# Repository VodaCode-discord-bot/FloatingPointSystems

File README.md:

# Floating Point Systems

A repository for gathering documentation and understanding Floating-Point-Systems machines.

> [!NOTE]
> This documentation is incomplete and will be expanded as more information becomes available.

> [!WARNING]
> This README needs to be verified by the REPO owner: Nakazoto. 

## Overview

This project contains datasheets, documentation, and code related to floating-point-sytems machines.

## Index - For README

1. [Overview](#overview) - Reason What this REPO is for. 
2. [Contents](#contents---of-each-folder) - What is in the Folders.
3. [Index for FPS](#index---for-the-folders) - Folder links.
4. [Contributing](#contributing) - Things to look out for.
    - [Guide on Contributing](#a-little-guide) - A guide on contributing.

## Contents - Of each folder

- Documentation on floating-point-systems
- Some Datasheets
- Photos of Cards, etc
- Code for the Machines

## Index - For the folders

1. [OLD](!Old/) - Folder with old stuff , _A trade of some sort_
2. [AP 120B](AP%20120B/) - Documetation folder for AP 120B, _the predecessor of the FPS 100._
3. [FPS 100](FPS%20100/) - Documetation folder for FPS 100, _the successor of the AP 120B. With redused cards._
4. [FPS 164](FPS%20164/) - Documetation folder for FPS 164, _the favorite machine of Usagi Electric._
5. [FPS 3000](FPS%203000/) - Documetation folder for FPS 3000, _the machine that only 1 still known to exist. And is almost the same as the XP 32 is._
6. [FPS 5000](FPS%205000/) - Documetation folder for FPS 5000, _As mentioned in fps.pdf, this is a family of the AP 120B, just like any other machine._
7. [Random FPS information](Z.%20Others/) - Documetation folder for FPS information, _Like part prices and boardrevisions._
8. [Random PDFs](Z_Brochures/) - Documetation folder for PDFs, _Like product pages and folders._
9. [Boards in FPS Machines](Cully_Dave.txt) - Documetation file for cards, _The card configuration on different machines._
10. [Magazine of some sort](Digital_Design_V12_N06_198206.pdf) - Some sort of Magazine.
11. [Boards](FPS%20Board%20List.txt) - A board series, _with documentation._
12. [Known Surviving](KnownSurviving.txt) - Documetation file for Surviving machines, _With name, place, condition and maybe price ;D_
13. [Want to make a FPS?](NewFPSLayout.txt) - Documetation file for A Complete Card set for AP 120B, _What some people have._

## Contributing

> [!CAUTION]
> This REPO is not meant for harassment, hating or any kind of destroying other people's work! So if you help this repo grow it is appreciated!

### A little guide:

> [!NOTE]
> _There are lots of guides online that explain this in detail._ [LINK](www.DID-NOT-FIND-ONE.com)

1. Create a Fork.
2. Import / Create the file you wanted to contribute.
3. Create a Pull request and explain what you changed.
	- You may have to add you fork (sometimes it does this automatically!)
4. Wait on a response!

> [!IMPORTANT]
> To to achieve your goal it needs to be relevant to the REPO and it's subject.

<!--
NOTE:
INDEX DOES NOT WORK IN EDITOR,
this is not done!
-->

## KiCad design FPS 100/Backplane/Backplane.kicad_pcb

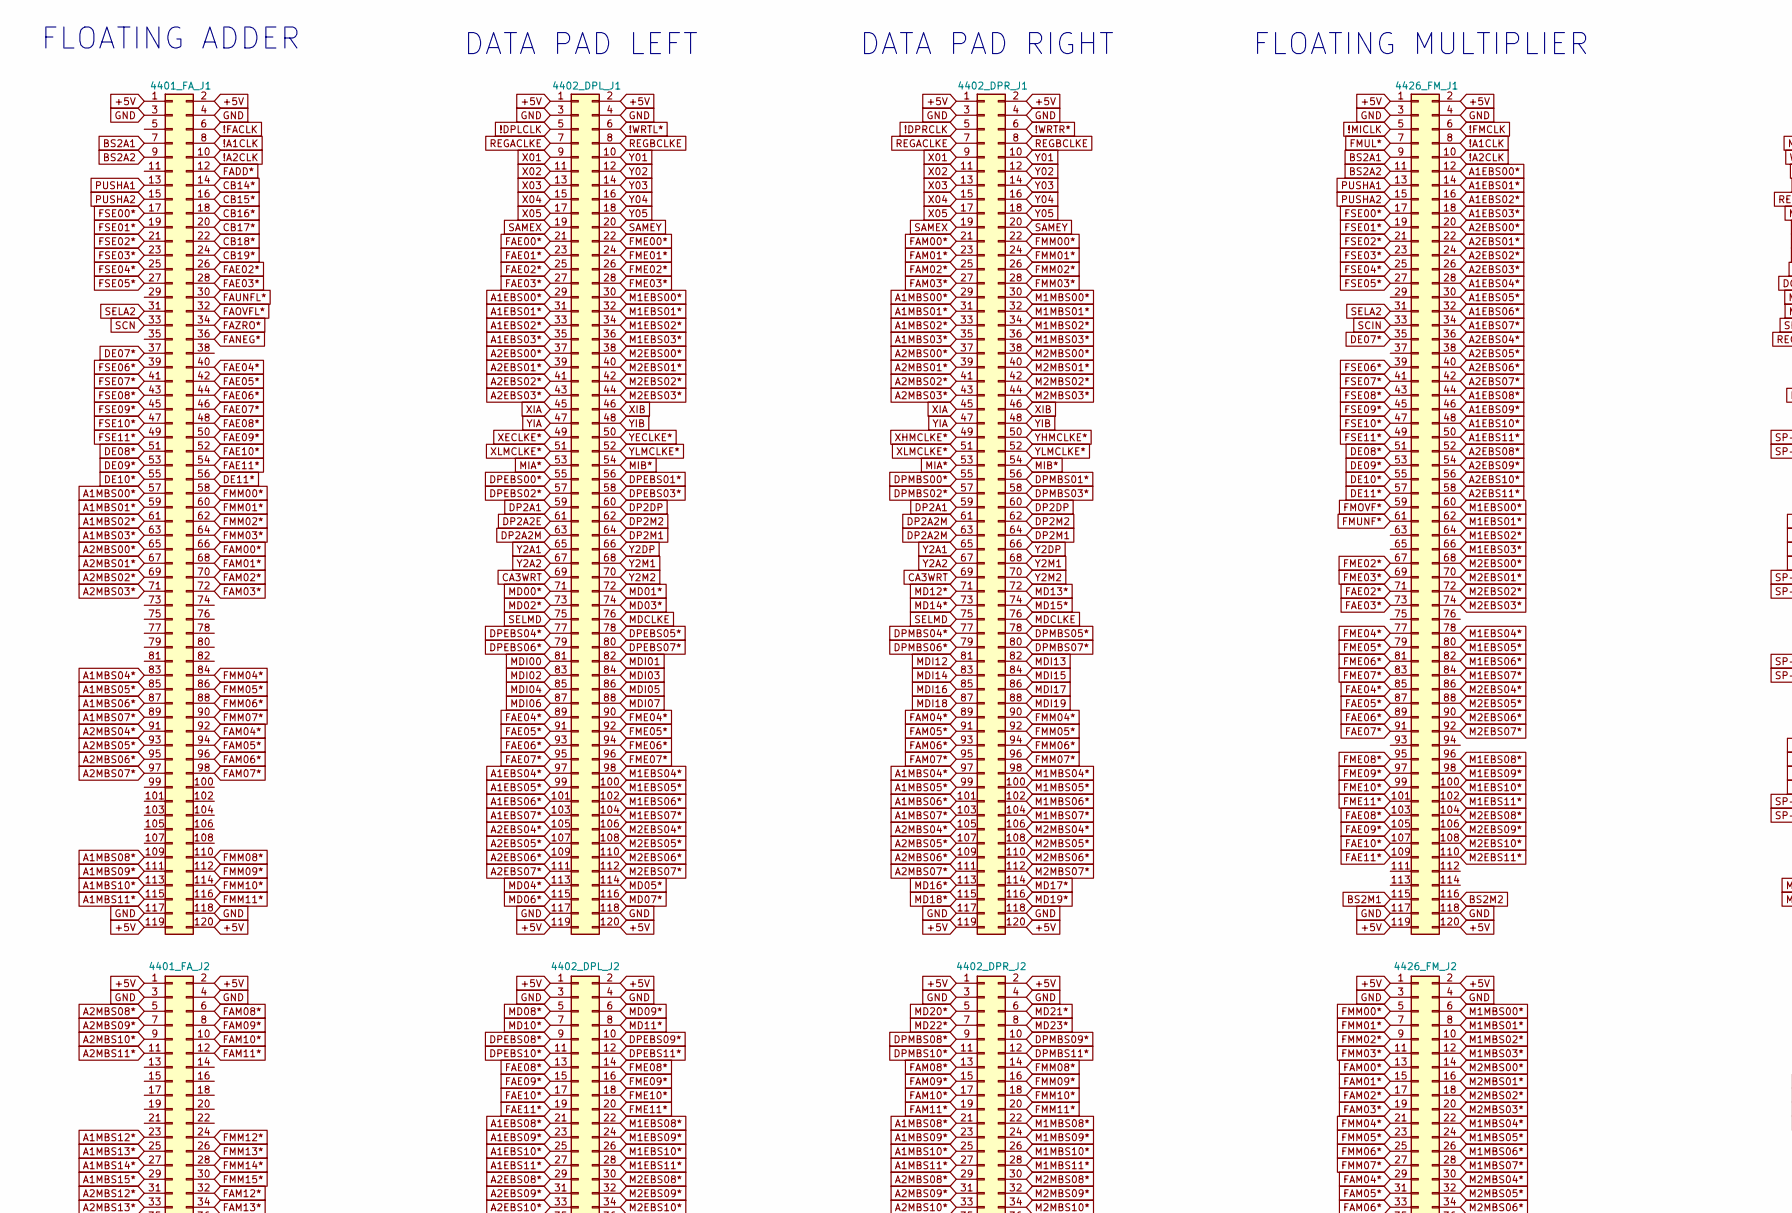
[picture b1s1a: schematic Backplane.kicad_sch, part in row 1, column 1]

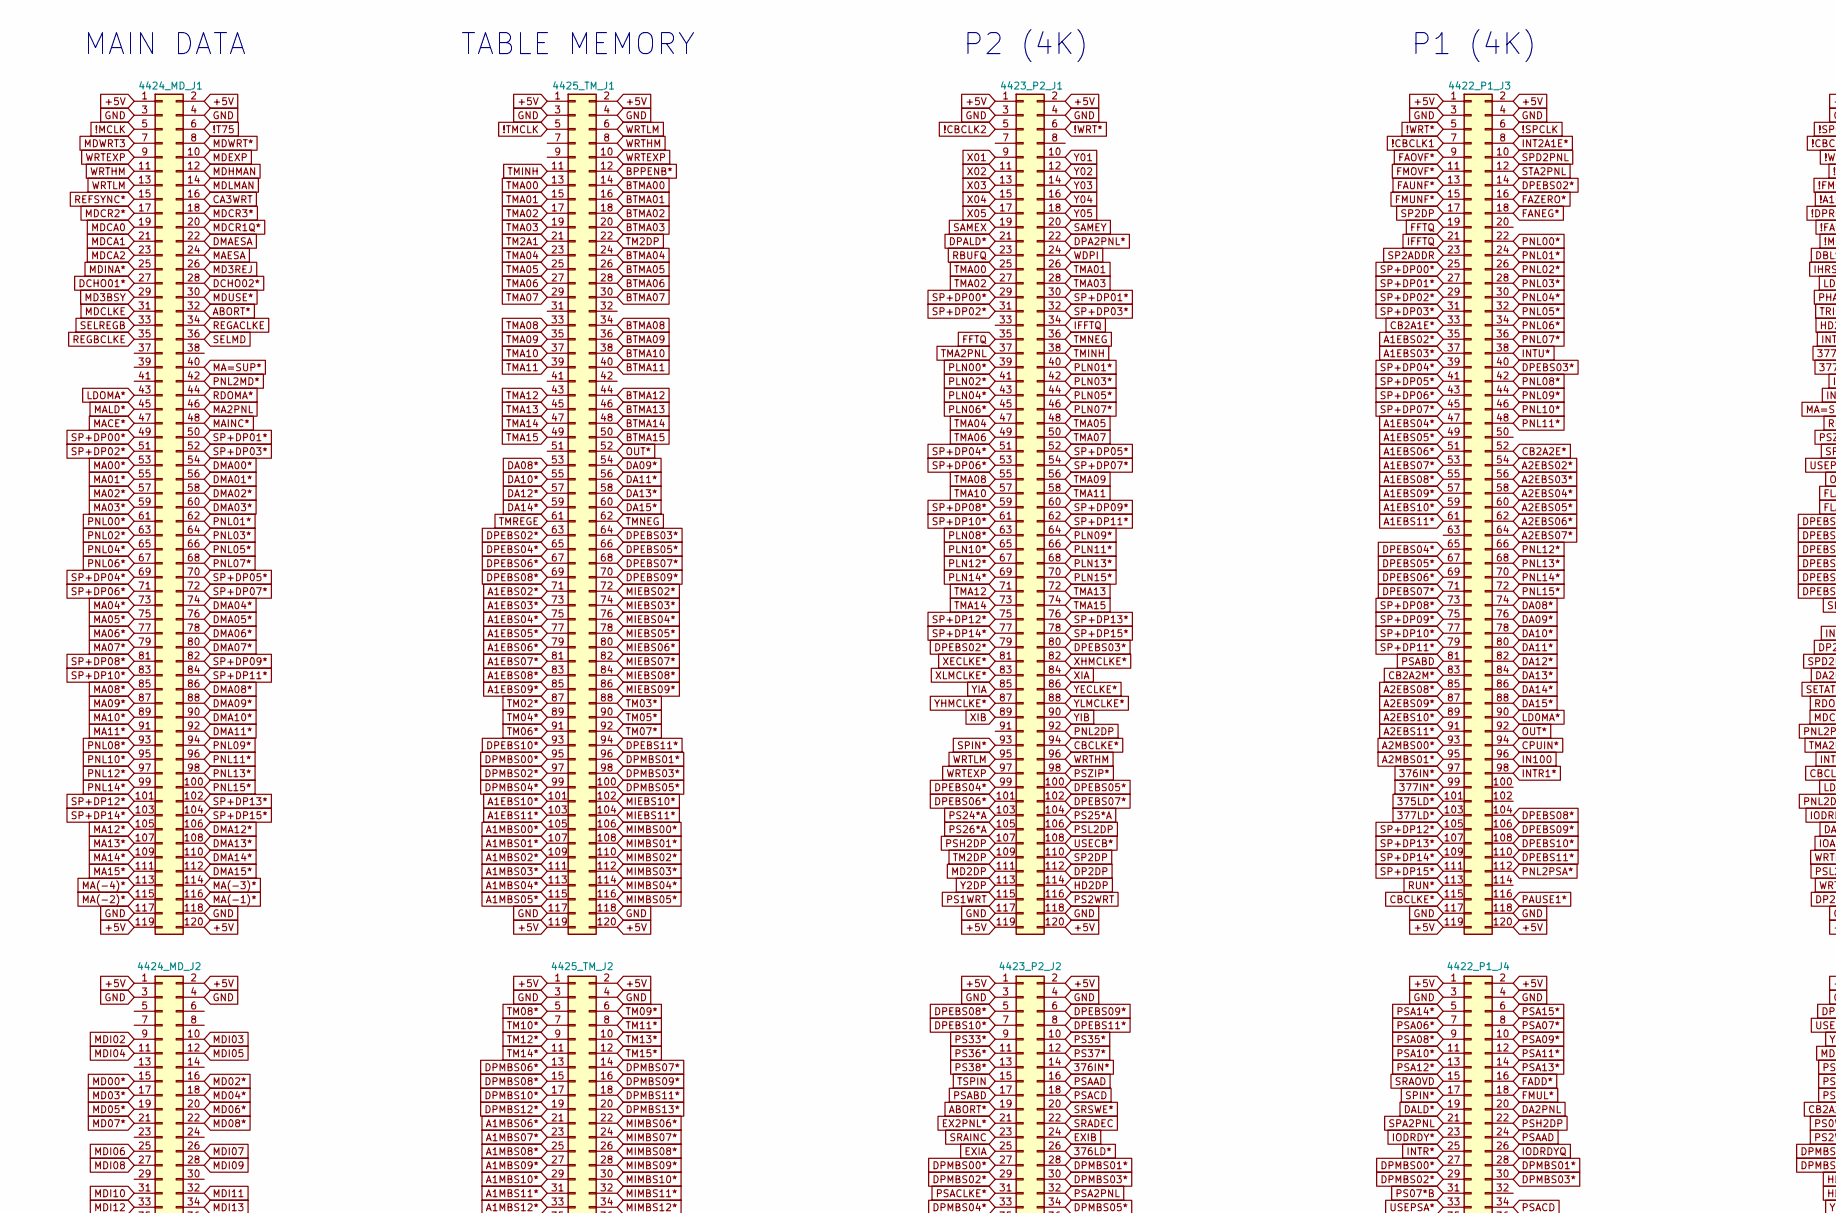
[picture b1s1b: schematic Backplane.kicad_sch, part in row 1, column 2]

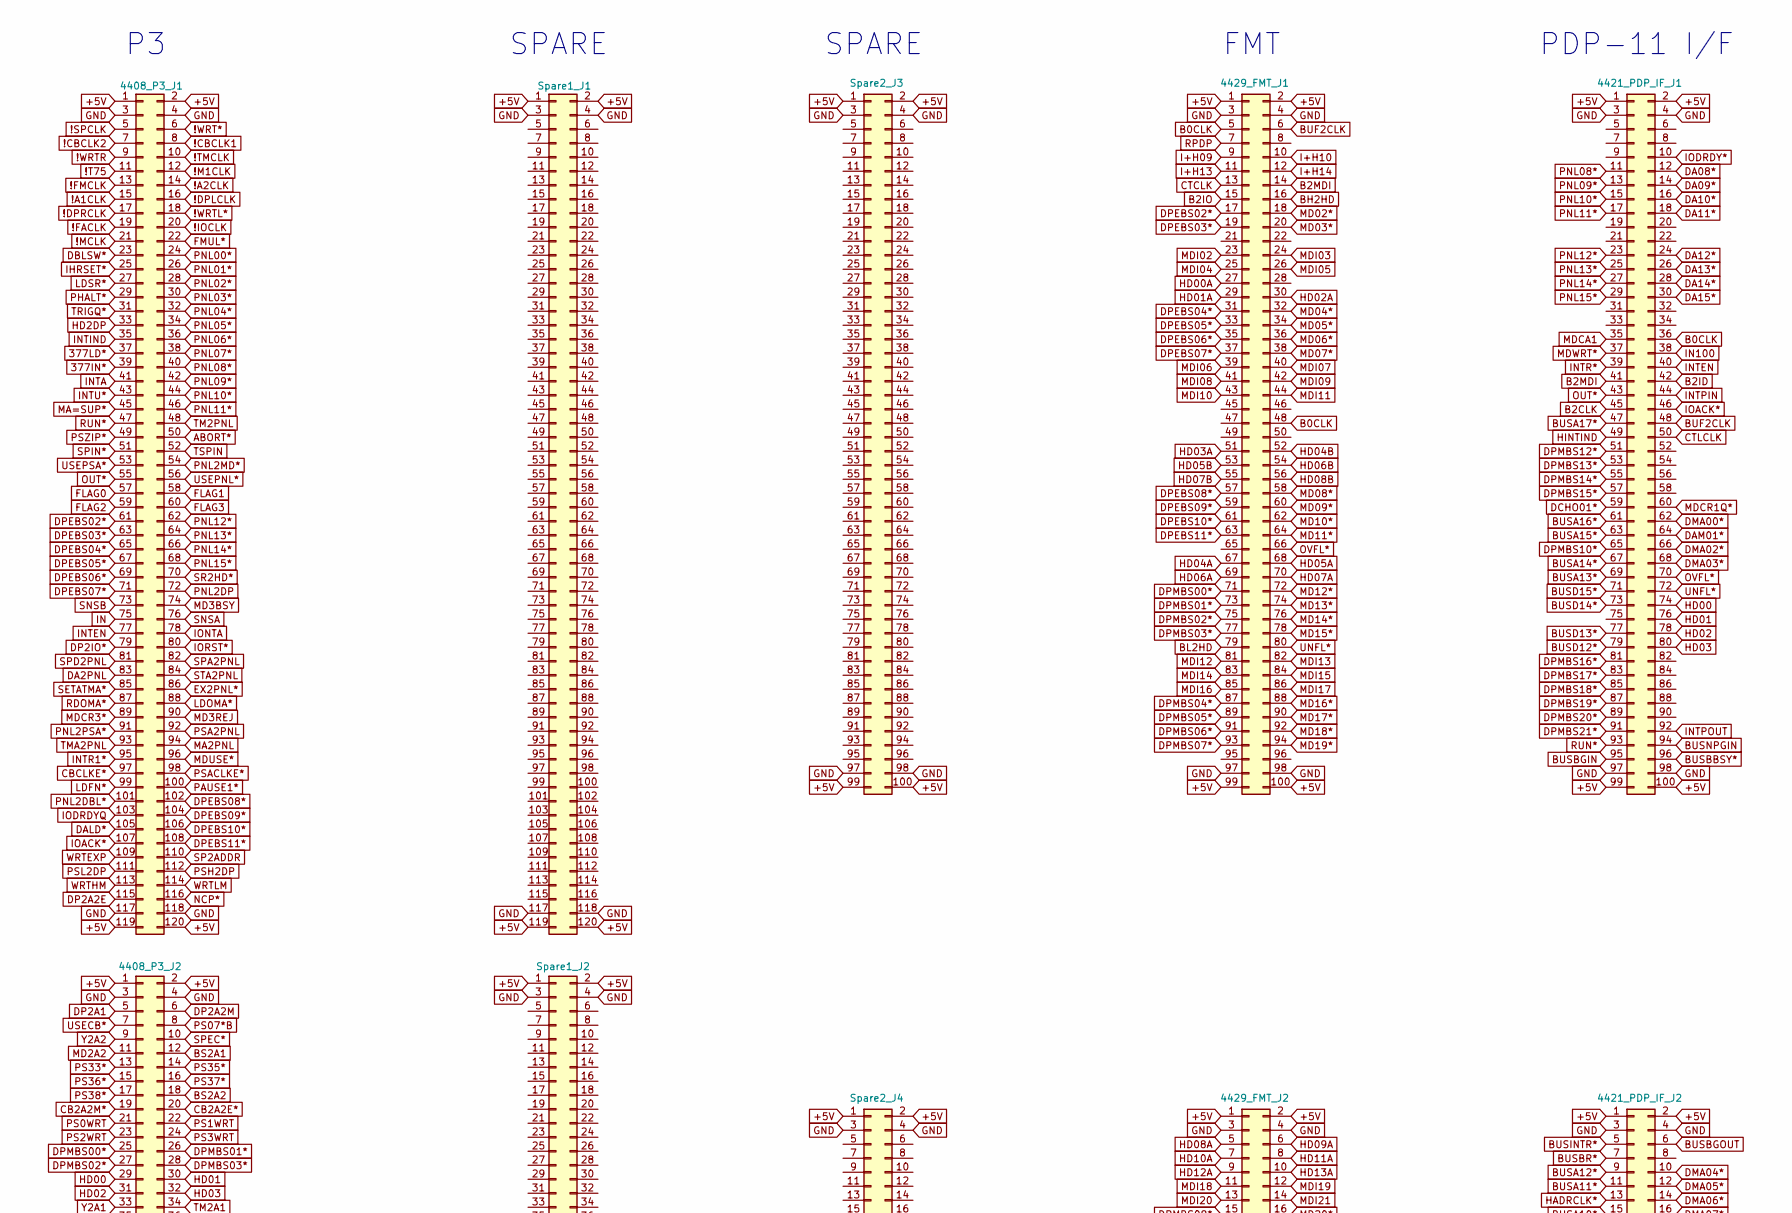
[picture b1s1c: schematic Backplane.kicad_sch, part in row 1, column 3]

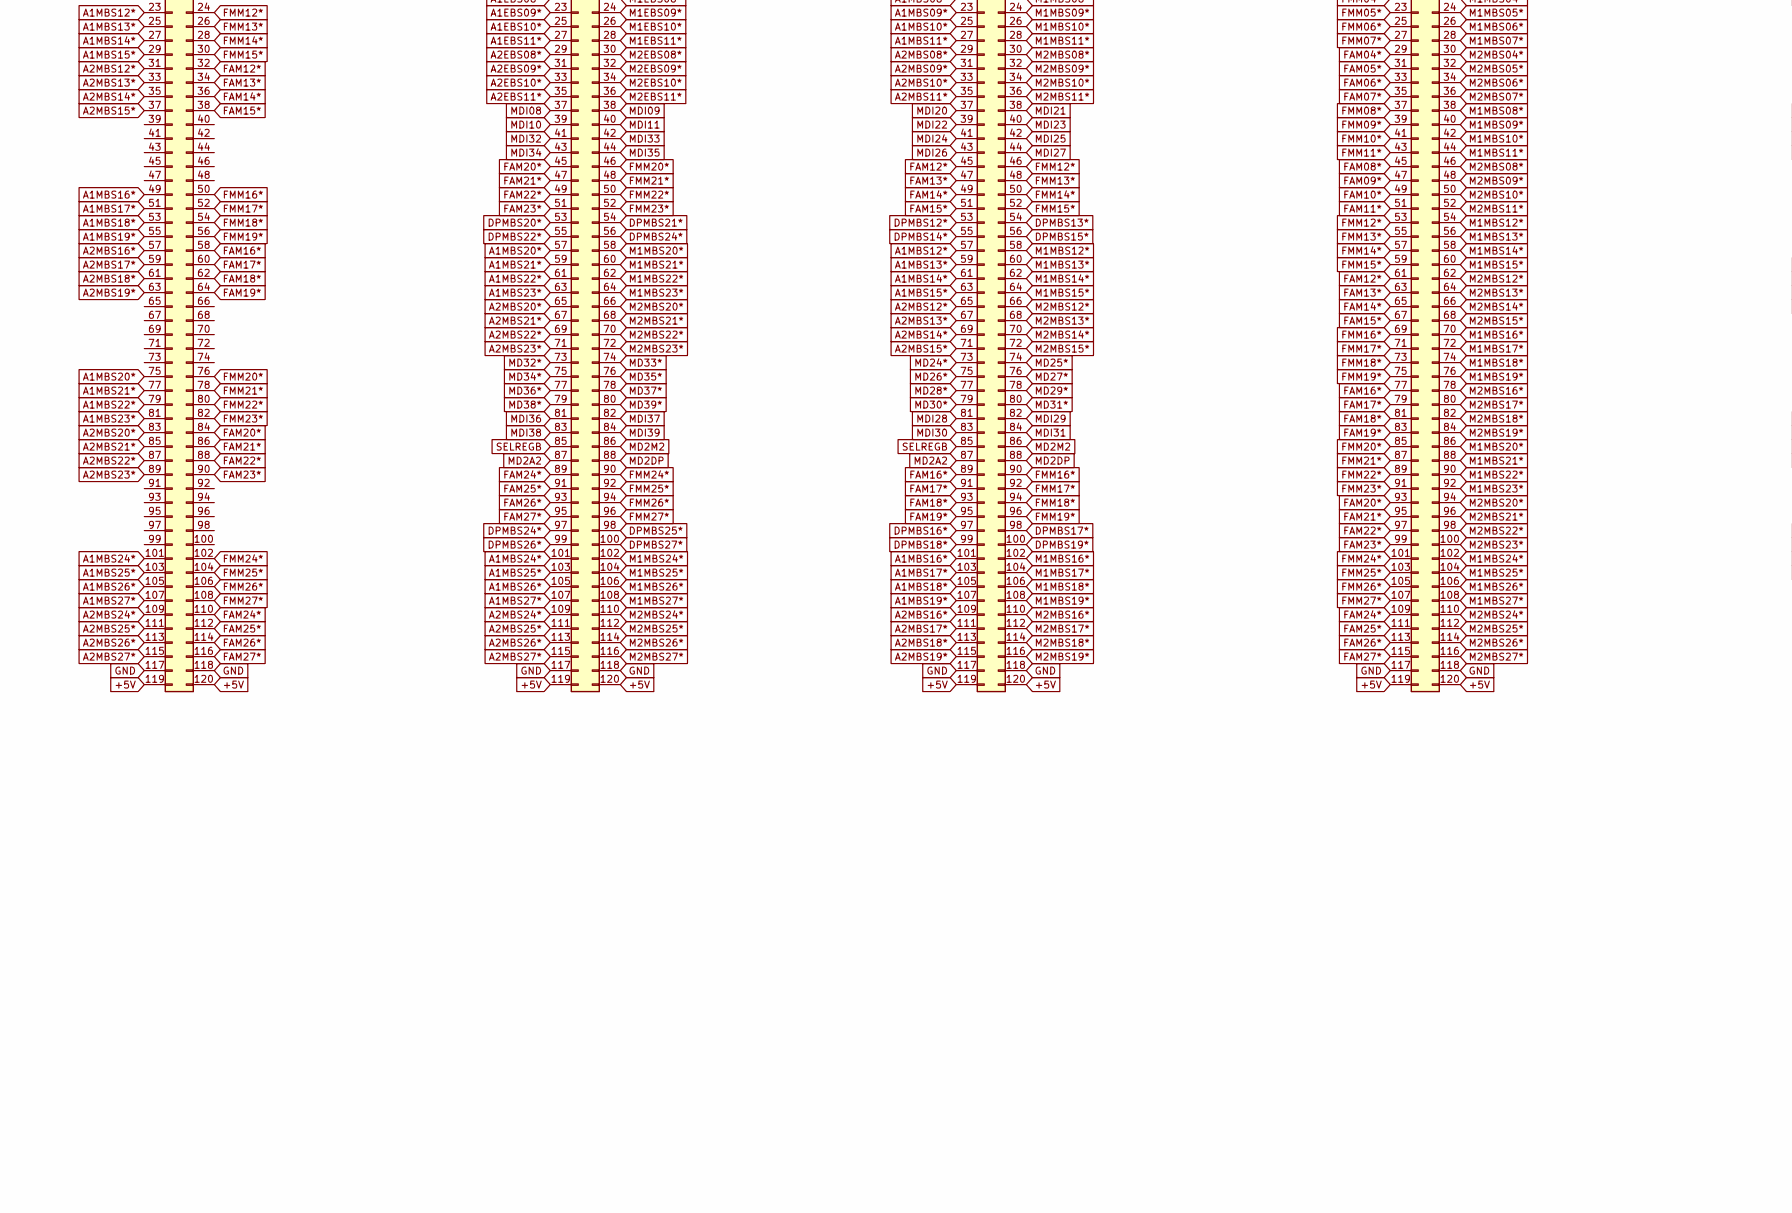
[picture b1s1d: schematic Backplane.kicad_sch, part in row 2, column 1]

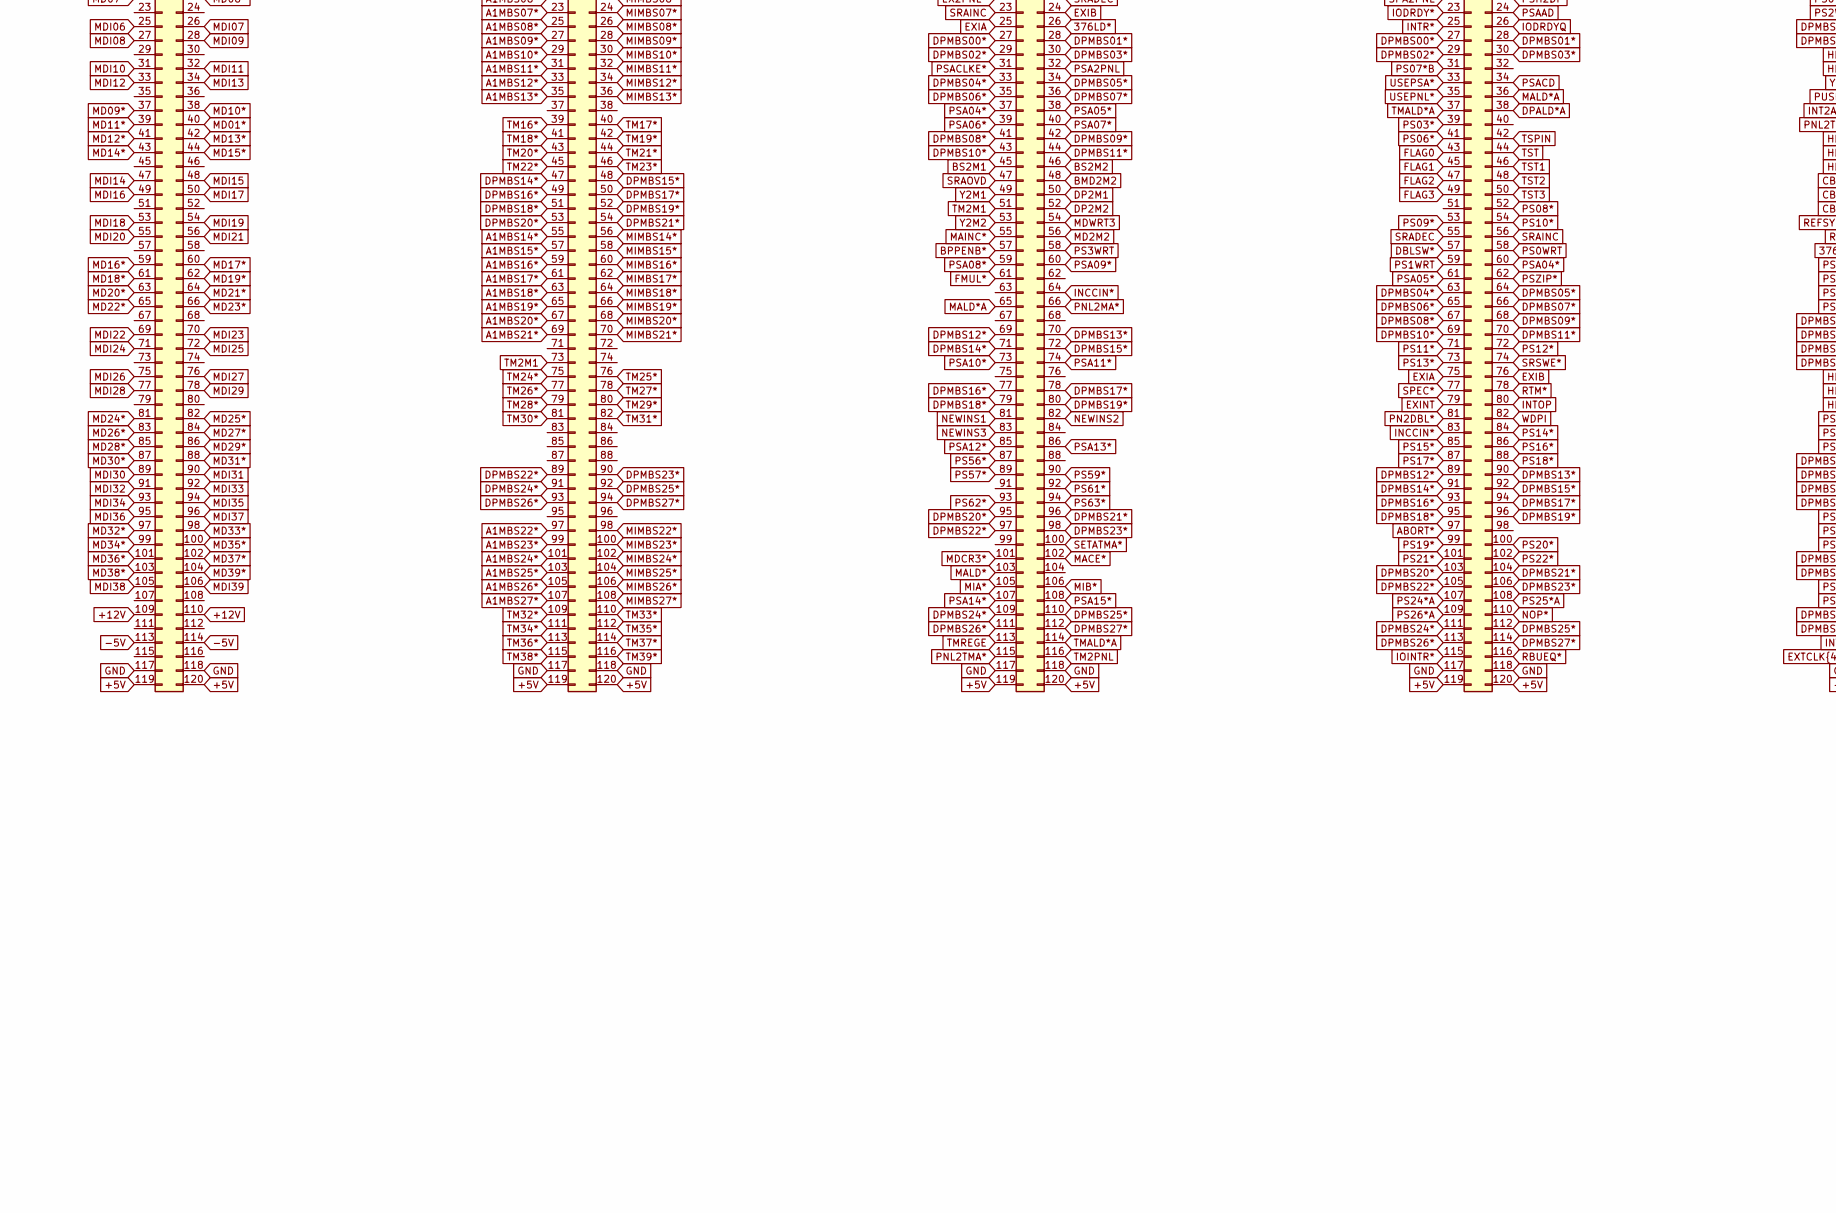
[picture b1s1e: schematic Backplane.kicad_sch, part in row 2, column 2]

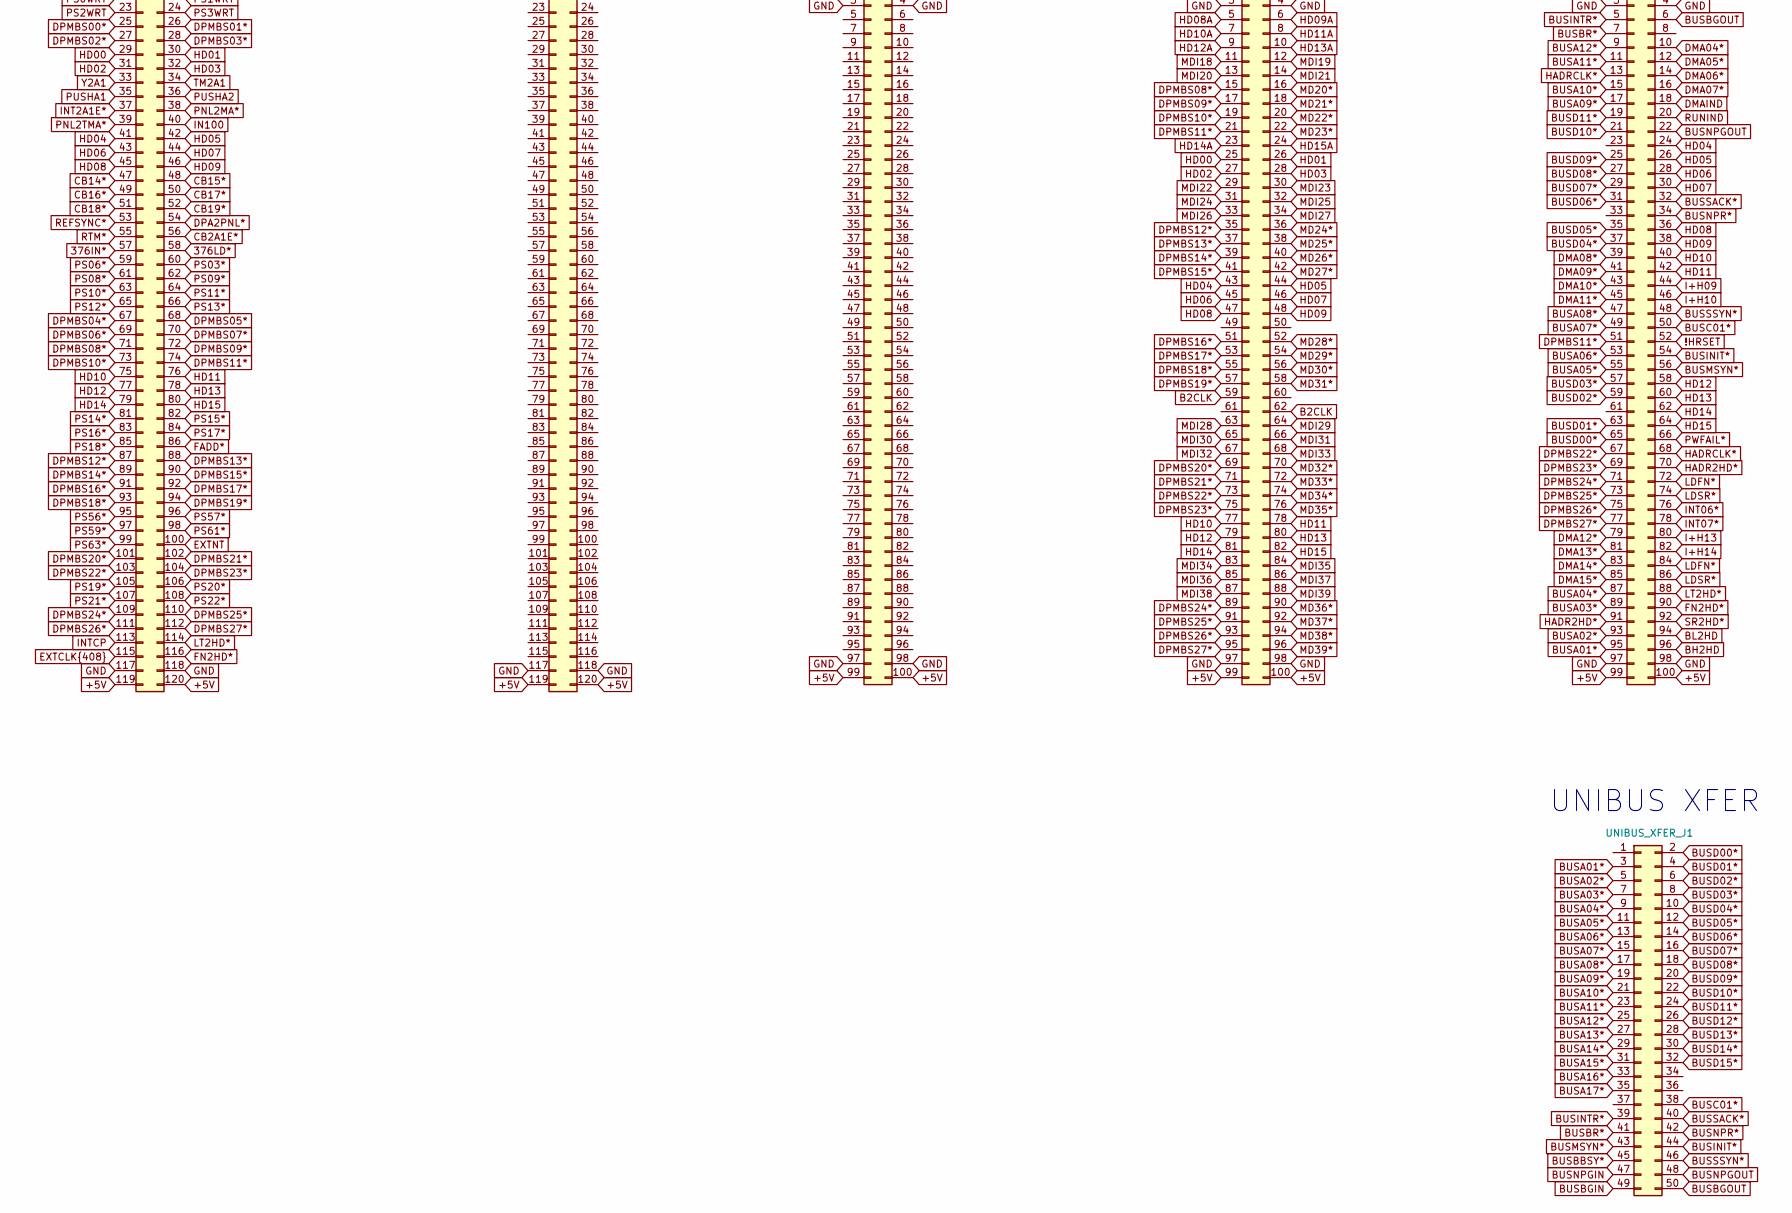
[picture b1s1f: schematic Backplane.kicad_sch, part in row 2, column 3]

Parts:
4401_FA_J1, 4401_FA_J2, 4402_DPL_J1, 4402_DPL_J2, 4402_DPR_J1, 4402_DPR_J2, 4408_P3_J1, 4408_P3_J2, 4422_P1_J3, 4422_P1_J4, 4423_P2_J1, 4423_P2_J2, 4424_MD_J1, 4424_MD_J2, 4425_TM_J1, 4425_TM_J2, 4426_FM_J1, 4426_FM_J2: Conn_02x60_120pin; 120pin_Edge_Connector
4421_PDP_IF_J1, 4421_PDP_IF_J2, 4429_FMT_J1, 4429_FMT_J2: Conn_02x50_100pin; 100pin_Edge_Connector
Spare1_J1, Spare1_J2: Conn_02x60_120pin; 120pin_Edge_Connector
Spare2_J3, Spare2_J4: Conn_02x50_100pin; 100pin_Edge_Connector
UNIBUS_XFER_J1: Conn_02x25_Odd_Even; PinHeader_2x25_P2.54mm_Vertical

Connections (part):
375LD*: 4422_P1_J3.101
376IN*: 4408_P3_J2.57, 4422_P1_J3.97, 4423_P2_J2.14
376LD*: 4408_P3_J2.58, 4423_P2_J2.26
377IN*: 4408_P3_J1.39, 4422_P1_J3.99
377LD*: 4408_P3_J1.37, 4422_P1_J3.103
!A1CLK: 4401_FA_J1.8, 4408_P3_J1.15, 4426_FM_J1.8
!A2CLK: 4401_FA_J1.10, 4408_P3_J1.14, 4426_FM_J1.10
!CBCLK1: 4408_P3_J1.8, 4422_P1_J3.7
!CBCLK2: 4408_P3_J1.7, 4423_P2_J1.5
!DPLCLK: 4402_DPL_J1.5, 4408_P3_J1.16
!DPRCLK: 4402_DPR_J1.5, 4408_P3_J1.17
!FACLK: 4401_FA_J1.6, 4408_P3_J1.19
!FMCLK: 4408_P3_J1.13, 4426_FM_J1.6
!HRSET: 4421_PDP_IF_J2.52
!IOCLK: 4408_P3_J1.20
!M1CLK: 4408_P3_J1.12
!MCLK: 4408_P3_J1.21, 4424_MD_J1.5
!MICLK: 4426_FM_J1.5
!SPCLK: 4408_P3_J1.5, 4422_P1_J3.6
!T75: 4408_P3_J1.11, 4424_MD_J1.6
!TMCLK: 4408_P3_J1.10, 4425_TM_J1.5
!WRT*: 4408_P3_J1.6, 4422_P1_J3.5, 4423_P2_J1.6
!WRTL*: 4402_DPL_J1.6, 4408_P3_J1.18
!WRTR: 4408_P3_J1.9
!WRTR*: 4402_DPR_J1.6
+5V: 4401_FA_J1.1, 4401_FA_J1.2, 4401_FA_J1.119, 4401_FA_J1.120, 4401_FA_J2.1, 4401_FA_J2.2, 4401_FA_J2.119, 4401_FA_J2.120, 4402_DPL_J1.1, 4402_DPL_J1.2, 4402_DPL_J1.119, 4402_DPL_J1.120, 4402_DPL_J2.1, 4402_DPL_J2.2, 4402_DPL_J2.119, 4402_DPL_J2.120, 4402_DPR_J1.1, 4402_DPR_J1.2, 4402_DPR_J1.119, 4402_DPR_J1.120, 4402_DPR_J2.1, 4402_DPR_J2.2, 4402_DPR_J2.119, 4402_DPR_J2.120, 4408_P3_J1.1, 4408_P3_J1.2, 4408_P3_J1.119, 4408_P3_J1.120, 4408_P3_J2.1, 4408_P3_J2.2, 4408_P3_J2.119, 4408_P3_J2.120, 4421_PDP_IF_J1.1, 4421_PDP_IF_J1.2, 4421_PDP_IF_J1.99, 4421_PDP_IF_J1.100, 4421_PDP_IF_J2.1, 4421_PDP_IF_J2.2, 4421_PDP_IF_J2.99, 4421_PDP_IF_J2.100, 4422_P1_J3.1, 4422_P1_J3.2, 4422_P1_J3.119, 4422_P1_J3.120, 4422_P1_J4.1, 4422_P1_J4.2, 4422_P1_J4.119, 4422_P1_J4.120, 4423_P2_J1.1, 4423_P2_J1.2, 4423_P2_J1.119, 4423_P2_J1.120, 4423_P2_J2.1, 4423_P2_J2.2, 4423_P2_J2.119, 4423_P2_J2.120, 4424_MD_J1.1, 4424_MD_J1.2, 4424_MD_J1.119, 4424_MD_J1.120, 4424_MD_J2.1, 4424_MD_J2.2, 4424_MD_J2.119, 4424_MD_J2.120, 4425_TM_J1.1, 4425_TM_J1.2, 4425_TM_J1.119, 4425_TM_J1.120, 4425_TM_J2.1, 4425_TM_J2.2, 4425_TM_J2.119, 4425_TM_J2.120, 4426_FM_J1.1, 4426_FM_J1.2, 4426_FM_J1.119, 4426_FM_J1.120, 4426_FM_J2.1, 4426_FM_J2.2, 4426_FM_J2.119, 4426_FM_J2.120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
+12V: 4424_MD_J2.109, 4424_MD_J2.110
-5V: 4424_MD_J2.113, 4424_MD_J2.114
A1EBS00*: 4402_DPL_J1.29, 4426_FM_J1.12
A1EBS01*: 4402_DPL_J1.31, 4426_FM_J1.14
A1EBS02*: 4402_DPL_J1.33, 4422_P1_J3.35, 4425_TM_J1.71, 4426_FM_J1.16
A1EBS03*: 4402_DPL_J1.35, 4422_P1_J3.37, 4425_TM_J1.73, 4426_FM_J1.18
A1EBS04*: 4402_DPL_J1.97, 4422_P1_J3.47, 4425_TM_J1.75, 4426_FM_J1.28
A1EBS05*: 4402_DPL_J1.99, 4422_P1_J3.49, 4425_TM_J1.77, 4426_FM_J1.30
A1EBS06*: 4402_DPL_J1.101, 4422_P1_J3.51, 4425_TM_J1.79, 4426_FM_J1.32
A1EBS07*: 4402_DPL_J1.103, 4422_P1_J3.53, 4425_TM_J1.81, 4426_FM_J1.34
A1EBS08*: 4402_DPL_J2.21, 4422_P1_J3.55, 4425_TM_J1.83, 4426_FM_J1.44
A1EBS09*: 4402_DPL_J2.23, 4422_P1_J3.57, 4425_TM_J1.85, 4426_FM_J1.46
A1EBS10*: 4402_DPL_J2.25, 4422_P1_J3.59, 4425_TM_J1.101, 4426_FM_J1.48
A1EBS11*: 4402_DPL_J2.27, 4422_P1_J3.61, 4425_TM_J1.103, 4426_FM_J1.50
A1MBS00*: 4401_FA_J1.57, 4402_DPR_J1.29, 4425_TM_J1.105
A1MBS01*: 4401_FA_J1.59, 4402_DPR_J1.31, 4425_TM_J1.107
A1MBS02*: 4401_FA_J1.61, 4402_DPR_J1.33, 4425_TM_J1.109
A1MBS03*: 4401_FA_J1.63, 4402_DPR_J1.35, 4425_TM_J1.111
A1MBS04*: 4401_FA_J1.83, 4402_DPR_J1.97, 4425_TM_J1.113
A1MBS05*: 4401_FA_J1.85, 4402_DPR_J1.99, 4425_TM_J1.115
A1MBS06*: 4401_FA_J1.87, 4402_DPR_J1.101, 4425_TM_J2.21
A1MBS07*: 4401_FA_J1.89, 4402_DPR_J1.103, 4425_TM_J2.23
A1MBS08*: 4401_FA_J1.109, 4402_DPR_J2.21, 4425_TM_J2.25
A1MBS09*: 4401_FA_J1.111, 4402_DPR_J2.23, 4425_TM_J2.27
A1MBS10*: 4401_FA_J1.113, 4402_DPR_J2.25, 4425_TM_J2.29
A1MBS11*: 4401_FA_J1.115, 4402_DPR_J2.27, 4425_TM_J2.31
A1MBS12*: 4401_FA_J2.23, 4402_DPR_J2.57, 4425_TM_J2.33
A1MBS13*: 4401_FA_J2.25, 4402_DPR_J2.59, 4425_TM_J2.35
A1MBS14*: 4401_FA_J2.27, 4402_DPR_J2.61, 4425_TM_J2.55
A1MBS15*: 4401_FA_J2.29, 4402_DPR_J2.63, 4425_TM_J2.57
A1MBS16*: 4401_FA_J2.49, 4402_DPR_J2.101, 4425_TM_J2.59
A1MBS17*: 4401_FA_J2.51, 4402_DPR_J2.103, 4425_TM_J2.61
A1MBS18*: 4401_FA_J2.53, 4402_DPR_J2.105, 4425_TM_J2.63
A1MBS19*: 4401_FA_J2.55, 4402_DPR_J2.107, 4425_TM_J2.65
A1MBS20*: 4401_FA_J2.75, 4402_DPL_J2.57, 4425_TM_J2.67
A1MBS21*: 4401_FA_J2.77, 4402_DPL_J2.59, 4425_TM_J2.69
A1MBS22*: 4401_FA_J2.79, 4402_DPL_J2.61, 4425_TM_J2.97
A1MBS23*: 4401_FA_J2.81, 4402_DPL_J2.63, 4425_TM_J2.99
A1MBS24*: 4401_FA_J2.101, 4402_DPL_J2.101, 4425_TM_J2.101
A1MBS25*: 4401_FA_J2.103, 4402_DPL_J2.103, 4425_TM_J2.103
A1MBS26*: 4401_FA_J2.105, 4402_DPL_J2.105, 4425_TM_J2.105
A1MBS27*: 4401_FA_J2.107, 4402_DPL_J2.107, 4425_TM_J2.107
A2EBS00*: 4402_DPL_J1.37, 4426_FM_J1.20
A2EBS01*: 4402_DPL_J1.39, 4426_FM_J1.22
A2EBS02*: 4402_DPL_J1.41, 4422_P1_J3.54, 4426_FM_J1.24
A2EBS03*: 4402_DPL_J1.43, 4422_P1_J3.56, 4426_FM_J1.26
A2EBS04*: 4402_DPL_J1.105, 4422_P1_J3.58, 4426_FM_J1.36
A2EBS05*: 4402_DPL_J1.107, 4422_P1_J3.60, 4426_FM_J1.38
A2EBS06*: 4402_DPL_J1.109, 4422_P1_J3.62, 4426_FM_J1.40
A2EBS07*: 4402_DPL_J1.111, 4422_P1_J3.64, 4426_FM_J1.42
A2EBS08*: 4402_DPL_J2.29, 4422_P1_J3.85, 4426_FM_J1.52
A2EBS09*: 4402_DPL_J2.31, 4422_P1_J3.87, 4426_FM_J1.54
A2EBS10*: 4402_DPL_J2.33, 4422_P1_J3.89, 4426_FM_J1.56
A2EBS11*: 4402_DPL_J2.35, 4422_P1_J3.91, 4426_FM_J1.58
A2MBS00*: 4401_FA_J1.65, 4402_DPR_J1.37, 4422_P1_J3.93
A2MBS01*: 4401_FA_J1.67, 4402_DPR_J1.39, 4422_P1_J3.95
A2MBS02*: 4401_FA_J1.69, 4402_DPR_J1.41
A2MBS03*: 4401_FA_J1.71, 4402_DPR_J1.43
A2MBS04*: 4401_FA_J1.91, 4402_DPR_J1.105
A2MBS05*: 4401_FA_J1.93, 4402_DPR_J1.107
A2MBS06*: 4401_FA_J1.95, 4402_DPR_J1.109
A2MBS07*: 4401_FA_J1.97, 4402_DPR_J1.111
A2MBS08*: 4401_FA_J2.5, 4402_DPR_J2.29
A2MBS09*: 4401_FA_J2.7, 4402_DPR_J2.31
A2MBS10*: 4401_FA_J2.9, 4402_DPR_J2.33
A2MBS11*: 4401_FA_J2.11, 4402_DPR_J2.35
A2MBS12*: 4401_FA_J2.31, 4402_DPR_J2.65
A2MBS13*: 4401_FA_J2.33, 4402_DPR_J2.67
A2MBS14*: 4401_FA_J2.35, 4402_DPR_J2.69
A2MBS15*: 4401_FA_J2.37, 4402_DPR_J2.71
A2MBS16*: 4401_FA_J2.57, 4402_DPR_J2.109
A2MBS17*: 4401_FA_J2.59, 4402_DPR_J2.111
A2MBS18*: 4401_FA_J2.61, 4402_DPR_J2.113
A2MBS19*: 4401_FA_J2.63, 4402_DPR_J2.115
A2MBS20*: 4401_FA_J2.83, 4402_DPL_J2.65
A2MBS21*: 4401_FA_J2.85, 4402_DPL_J2.67
A2MBS22*: 4401_FA_J2.87, 4402_DPL_J2.69
A2MBS23*: 4401_FA_J2.89, 4402_DPL_J2.71
A2MBS24*: 4401_FA_J2.109, 4402_DPL_J2.109
A2MBS25*: 4401_FA_J2.111, 4402_DPL_J2.111
A2MBS26*: 4401_FA_J2.113, 4402_DPL_J2.113
A2MBS27*: 4401_FA_J2.115, 4402_DPL_J2.115
ABORT*: 4408_P3_J1.50, 4422_P1_J4.97, 4423_P2_J2.19, 4424_MD_J1.32
B0CLK: 4421_PDP_IF_J1.36, 4429_FMT_J1.5, 4429_FMT_J1.48
B2CLK: 4421_PDP_IF_J1.45, 4429_FMT_J2.59, 4429_FMT_J2.62
B2ID: 4421_PDP_IF_J1.42
B2IO: 4429_FMT_J1.15
B2MDI: 4421_PDP_IF_J1.41, 4429_FMT_J1.14
BH2HD: 4421_PDP_IF_J2.96, 4429_FMT_J1.16
BL2HD: 4421_PDP_IF_J2.94, 4429_FMT_J1.79
BMD2M2: 4423_P2_J2.48
BPPENB*: 4423_P2_J2.57, 4425_TM_J1.12
BS2A1: 4401_FA_J1.7, 4408_P3_J2.12, 4426_FM_J1.9
BS2A2: 4401_FA_J1.9, 4408_P3_J2.18, 4426_FM_J1.11
BS2M1: 4423_P2_J2.45, 4426_FM_J1.115
BS2M2: 4423_P2_J2.46, 4426_FM_J1.116
BTMA00: 4425_TM_J1.14
BTMA01: 4425_TM_J1.16
BTMA02: 4425_TM_J1.18
BTMA03: 4425_TM_J1.20
BTMA04: 4425_TM_J1.24
BTMA05: 4425_TM_J1.26
BTMA06: 4425_TM_J1.28
BTMA07: 4425_TM_J1.30
BTMA08: 4425_TM_J1.34
BTMA09: 4425_TM_J1.36
BTMA10: 4425_TM_J1.38
BTMA11: 4425_TM_J1.40
BTMA12: 4425_TM_J1.44
BTMA13: 4425_TM_J1.46
BTMA14: 4425_TM_J1.48
BTMA15: 4425_TM_J1.50
BUF2CLK: 4421_PDP_IF_J1.48, 4429_FMT_J1.6
BUSA01*: 4421_PDP_IF_J2.95, UNIBUS_XFER_J1.3
BUSA02*: 4421_PDP_IF_J2.93, UNIBUS_XFER_J1.5
BUSA03*: 4421_PDP_IF_J2.89, UNIBUS_XFER_J1.7
BUSA04*: 4421_PDP_IF_J2.87, UNIBUS_XFER_J1.9
BUSA05*: 4421_PDP_IF_J2.55, UNIBUS_XFER_J1.11
BUSA06*: 4421_PDP_IF_J2.53, UNIBUS_XFER_J1.13
BUSA07*: 4421_PDP_IF_J2.49, UNIBUS_XFER_J1.15
BUSA08*: 4421_PDP_IF_J2.47, UNIBUS_XFER_J1.17
BUSA09*: 4421_PDP_IF_J2.17, UNIBUS_XFER_J1.19
BUSA10*: 4421_PDP_IF_J2.15, UNIBUS_XFER_J1.21
BUSA11*: 4421_PDP_IF_J2.11, UNIBUS_XFER_J1.23
BUSA12*: 4421_PDP_IF_J2.9, UNIBUS_XFER_J1.25
BUSA13*: 4421_PDP_IF_J1.69, UNIBUS_XFER_J1.27
BUSA14*: 4421_PDP_IF_J1.67, UNIBUS_XFER_J1.29
BUSA15*: 4421_PDP_IF_J1.63, UNIBUS_XFER_J1.31
BUSA16*: 4421_PDP_IF_J1.61, UNIBUS_XFER_J1.33
BUSA17*: 4421_PDP_IF_J1.47, UNIBUS_XFER_J1.35
BUSBBSY*: 4421_PDP_IF_J1.96, UNIBUS_XFER_J1.45
BUSBGIN: 4421_PDP_IF_J1.95, UNIBUS_XFER_J1.49
BUSBGOUT: 4421_PDP_IF_J2.6, UNIBUS_XFER_J1.50
BUSBR*: 4421_PDP_IF_J2.7, UNIBUS_XFER_J1.41
BUSC01*: 4421_PDP_IF_J2.50, UNIBUS_XFER_J1.38
BUSD00*: 4421_PDP_IF_J2.65, UNIBUS_XFER_J1.2
BUSD01*: 4421_PDP_IF_J2.63, UNIBUS_XFER_J1.4
BUSD02*: 4421_PDP_IF_J2.59, UNIBUS_XFER_J1.6
BUSD03*: 4421_PDP_IF_J2.57, UNIBUS_XFER_J1.8
BUSD04*: 4421_PDP_IF_J2.37, UNIBUS_XFER_J1.10
BUSD05*: 4421_PDP_IF_J2.35, UNIBUS_XFER_J1.12
BUSD06*: 4421_PDP_IF_J2.31, UNIBUS_XFER_J1.14
BUSD07*: 4421_PDP_IF_J2.29, UNIBUS_XFER_J1.16
BUSD08*: 4421_PDP_IF_J2.27, UNIBUS_XFER_J1.18
BUSD09*: 4421_PDP_IF_J2.25, UNIBUS_XFER_J1.20
BUSD10*: 4421_PDP_IF_J2.21, UNIBUS_XFER_J1.22
BUSD11*: 4421_PDP_IF_J2.19, UNIBUS_XFER_J1.24
BUSD12*: 4421_PDP_IF_J1.79, UNIBUS_XFER_J1.26
BUSD13*: 4421_PDP_IF_J1.77, UNIBUS_XFER_J1.28
BUSD14*: 4421_PDP_IF_J1.73, UNIBUS_XFER_J1.30
BUSD15*: 4421_PDP_IF_J1.71, UNIBUS_XFER_J1.32
BUSINIT*: 4421_PDP_IF_J2.54, UNIBUS_XFER_J1.44
BUSINTR*: 4421_PDP_IF_J2.5, UNIBUS_XFER_J1.39
BUSMSYN*: 4421_PDP_IF_J2.56, UNIBUS_XFER_J1.43
BUSNPGIN: 4421_PDP_IF_J1.94, UNIBUS_XFER_J1.47
BUSNPGOUT: 4421_PDP_IF_J2.22, UNIBUS_XFER_J1.48
BUSNPR*: 4421_PDP_IF_J2.34, UNIBUS_XFER_J1.42
BUSSACK*: 4421_PDP_IF_J2.32, UNIBUS_XFER_J1.40
BUSSSYN*: 4421_PDP_IF_J2.48, UNIBUS_XFER_J1.46
CA3WRT: 4402_DPL_J1.69, 4402_DPR_J1.69, 4424_MD_J1.16
CB2A1E*: 4408_P3_J2.56, 4422_P1_J3.33
CB2A2E*: 4408_P3_J2.20, 4422_P1_J3.52
CB2A2M*: 4408_P3_J2.19, 4422_P1_J3.83
CB14*: 4401_FA_J1.14, 4408_P3_J2.47
CB15*: 4401_FA_J1.16, 4408_P3_J2.48
CB16*: 4401_FA_J1.18, 4408_P3_J2.49
CB17*: 4401_FA_J1.20, 4408_P3_J2.50
CB18*: 4401_FA_J1.22, 4408_P3_J2.51
CB19*: 4401_FA_J1.24, 4408_P3_J2.52
CBCLKE*: 4408_P3_J1.97, 4422_P1_J3.115, 4423_P2_J1.94
CPUIN*: 4422_P1_J3.94
CTCLK: 4429_FMT_J1.13
CTLCLK: 4421_PDP_IF_J1.50
DA2PNL: 4408_P3_J1.83, 4422_P1_J4.20
DA08*: 4421_PDP_IF_J1.12, 4422_P1_J3.74, 4425_TM_J1.53
DA09*: 4421_PDP_IF_J1.14, 4422_P1_J3.76, 4425_TM_J1.54
DA10*: 4421_PDP_IF_J1.16, 4422_P1_J3.78, 4425_TM_J1.55
DA11*: 4421_PDP_IF_J1.18, 4422_P1_J3.80, 4425_TM_J1.56
DA12*: 4421_PDP_IF_J1.24, 4422_P1_J3.82, 4425_TM_J1.57
DA13*: 4421_PDP_IF_J1.26, 4422_P1_J3.84, 4425_TM_J1.58
DA14*: 4421_PDP_IF_J1.28, 4422_P1_J3.86, 4425_TM_J1.59
DA15*: 4421_PDP_IF_J1.30, 4422_P1_J3.88, 4425_TM_J1.60
DALD*: 4408_P3_J1.105, 4422_P1_J4.19
DAM01*: 4421_PDP_IF_J1.64
DBLSW*: 4408_P3_J1.23, 4422_P1_J4.57
DCHO01*: 4421_PDP_IF_J1.59, 4424_MD_J1.27
DCHO02*: 4424_MD_J1.28
DE07*: 4401_FA_J1.37, 4426_FM_J1.35
DE08*: 4401_FA_J1.51, 4426_FM_J1.51
DE09*: 4401_FA_J1.53, 4426_FM_J1.53
DE10*: 4401_FA_J1.55, 4426_FM_J1.55
DE11*: 4401_FA_J1.56, 4426_FM_J1.57
DMA00*: 4421_PDP_IF_J1.62, 4424_MD_J1.54
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
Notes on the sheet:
P2 (4K)
FLOATING MULTIPLIER
PDP-11 I/F
FLOATING ADDER
FMT
DATA PAD RIGHT
UNIBUS XFER
SPARE
MAIN DATA
P1 (4K)
DATA PAD LEFT
TABLE MEMORY

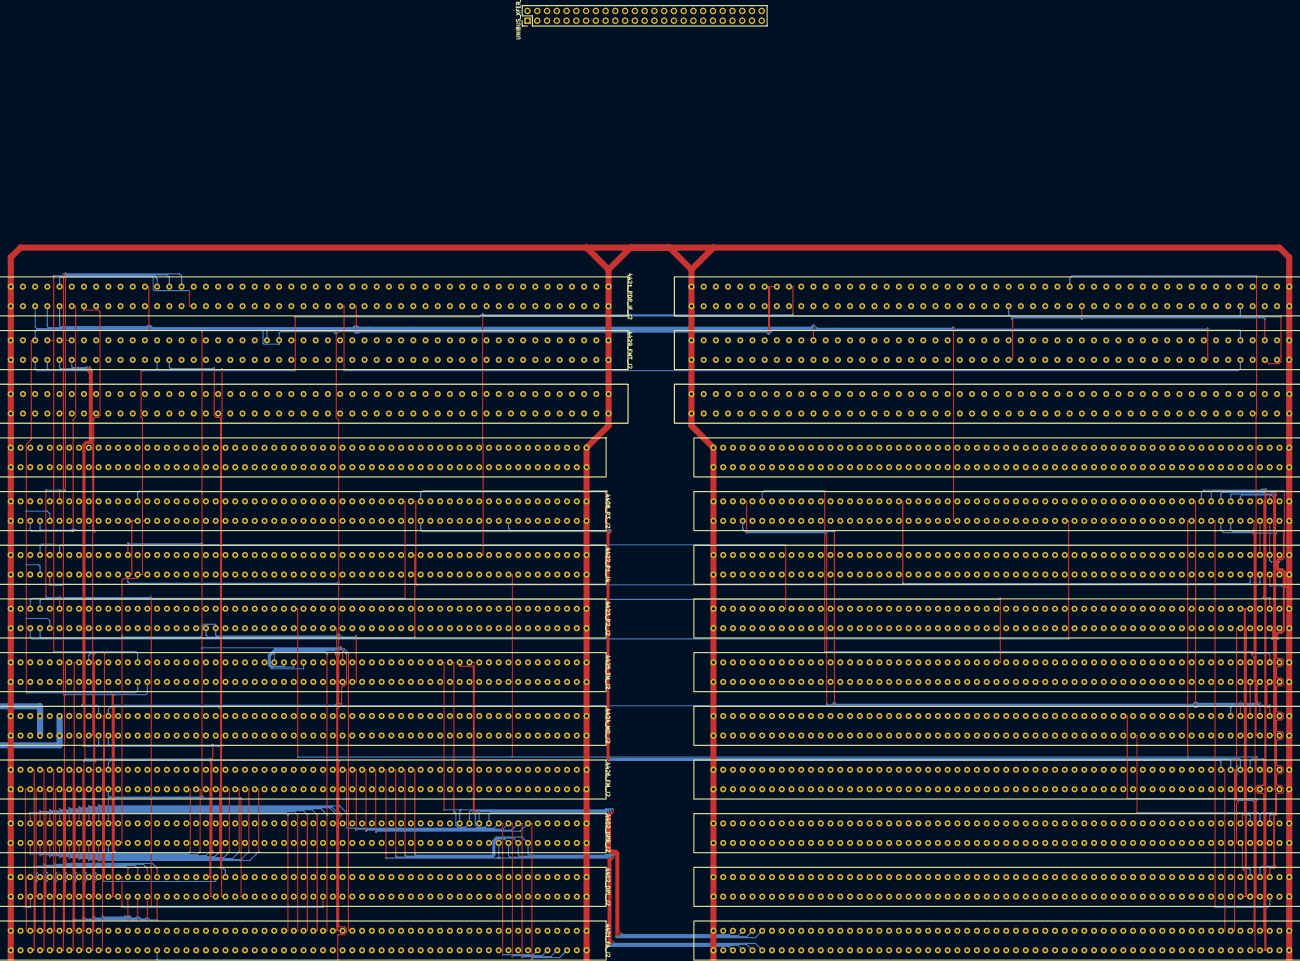
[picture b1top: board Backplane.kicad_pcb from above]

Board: 6 copper layers, 27 parts (0 on the bottom side), 746 nets.

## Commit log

2025-07-27 2025/7/27
2025-08-09 2025/8/9
2025-08-12 2025/8/11
2026-01-02 2026/1/2
2026-01-04 Update links in README index for FPS folders
2026-01-04 Revise README structure and link formatting
    Updated the README to improve structure and links.
2026-01-04 Update README with verification and warning notes
2026-01-04 Revise README index and folder links
    Updated links and descriptions in the README for clarity.
2026-01-04 Revise README.md for clarity and accuracy
    Updated documentation entries and corrected typos.
